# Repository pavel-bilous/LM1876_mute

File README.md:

# LM1876 mute delay

Circuit mutes LM1876 for 1 sec upon powering on. 

From the datasheet, if a logic high (1.5 to 5V) is applied to the MUTE pin, the amp will be muted.

The goal is to mute the amp during the turn on (and turn off). For that a logic high needs to be applied to the MUTE pin when amp is turned on, but after 1 or 2 seconds wait time the MUTE pin should be pulled low (< 1.5V).

Simple circuit that achieves the goal consists of:
* 5V zener regulator
* RC time delay
* NOT logic gate

Power is taken from the positive rail of the amp's power supply that is 20V to 25V.

Zener regulator resistor is selected at 10K, and it pulls ~2mA of current. Another 10K resistor is at the drain of the FET and pulls another ~2mA resulting in total current draw of ~4mA.

## PCB rendered in 3d:

## Schematics
Only one 22uF capacitor needs to be used.

## PCB layout

Headers can be directly connected on top of the amplifier board in my other repository for LM1876 board.

## LTSpice simulation

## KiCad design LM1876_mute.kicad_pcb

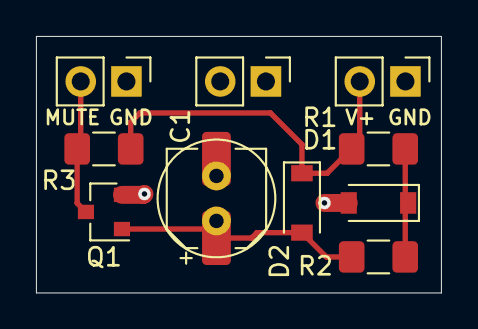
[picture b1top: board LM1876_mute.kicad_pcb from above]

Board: 2 copper layers, 22.5 x 14.2 mm, 11 parts (0 on the bottom side), 5 nets.

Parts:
C1: 22u; CP_Elec_5x5.4
C2: 22u; C_Radial_D6.3mm_H5.0mm_P2.50mm
D1: BZT52Bxx; D_SOD-123
D2: 1N4148W; D_SOD-123
J3: POWER_HEADER; PinHeader_1x02_P2.54mm_Vertical
J4: MUTE_HEADER; PinHeader_1x02_P2.54mm_Vertical
J5: STBY; PinHeader_1x02_P2.54mm_Vertical
Q1: 2N7002; SOT-23
R1, R3: 10K; R_1206_3216Metric_Pad1.42x1.75mm_HandSolder
R2: 100K; R_1206_3216Metric_Pad1.42x1.75mm_HandSolder

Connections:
/5V_ZENER: D1.1, R1.1, R2.2
/GATE: C1.1, C2.1, D2.2, Q1.1, R2.1
GND: C1.2, C2.2, D1.2, J3.1, J4.1, Q1.2
MUTE: J4.2, Q1.3, R3.1
V+: D2.1, J3.2, R1.2, R3.2

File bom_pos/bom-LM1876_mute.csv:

"Id";"Designator";"Package";"Quantity";"Designation";"Supplier and ref";
1;"C2";"C_Radial_D6.3mm_H5.0mm_P2.50mm";1;"22u";;;
2;"C1";"CP_Elec_5x5.4";1;"22u";;;
3;"J5";"PinHeader_1x02_P2.54mm_Vertical";1;"STBY";;;
4;"R3,R1";"R_1206_3216Metric_Pad1.42x1.75mm_HandSolder";2;"10K";;;
5;"R2";"R_1206_3216Metric_Pad1.42x1.75mm_HandSolder";1;"100K";;;
6;"Q1";"SOT-23";1;"2N7002";;;
7;"J4";"PinHeader_1x02_P2.54mm_Vertical";1;"MUTE_HEADER";;;
8;"J3";"PinHeader_1x02_P2.54mm_Vertical";1;"POWER_HEADER";;;
9;"D2";"D_SOD-123";1;"1N4148W";;;
10;"D1";"D_SOD-123";1;"BZT52Bxx";;;

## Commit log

2023-05-09 added imgs
2023-05-09 added simulation fles
